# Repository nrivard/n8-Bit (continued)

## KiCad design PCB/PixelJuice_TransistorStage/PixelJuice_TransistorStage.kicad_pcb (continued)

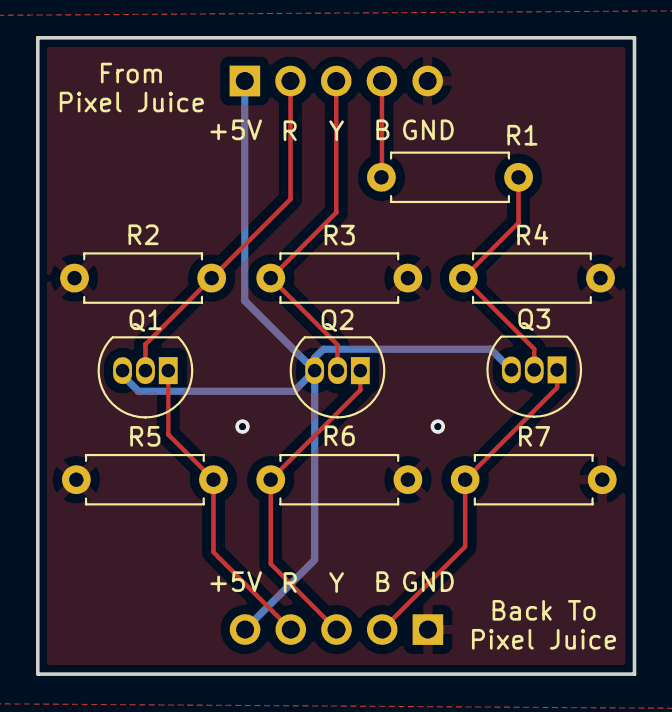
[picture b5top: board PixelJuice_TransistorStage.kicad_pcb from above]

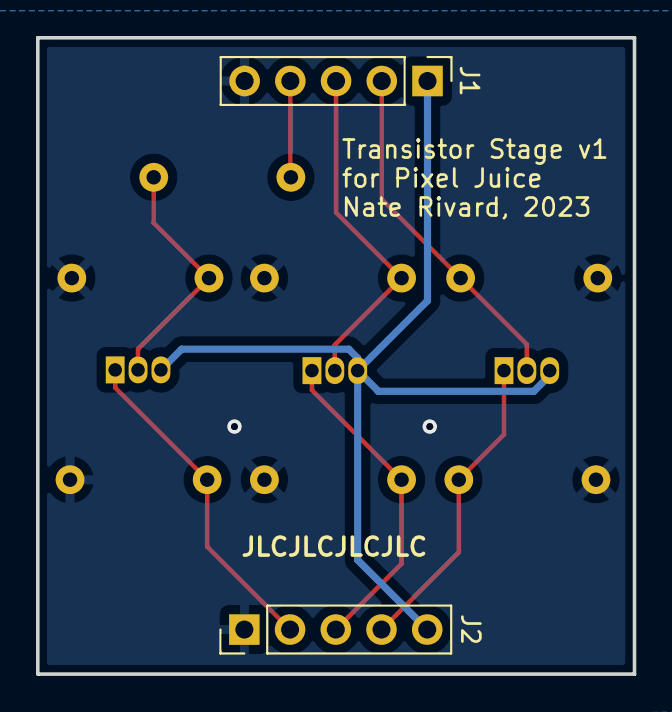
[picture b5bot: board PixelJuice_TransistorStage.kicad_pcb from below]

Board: 2 copper layers, 33.2 x 35.3 mm, 12 parts (2 on the bottom side), 9 nets.

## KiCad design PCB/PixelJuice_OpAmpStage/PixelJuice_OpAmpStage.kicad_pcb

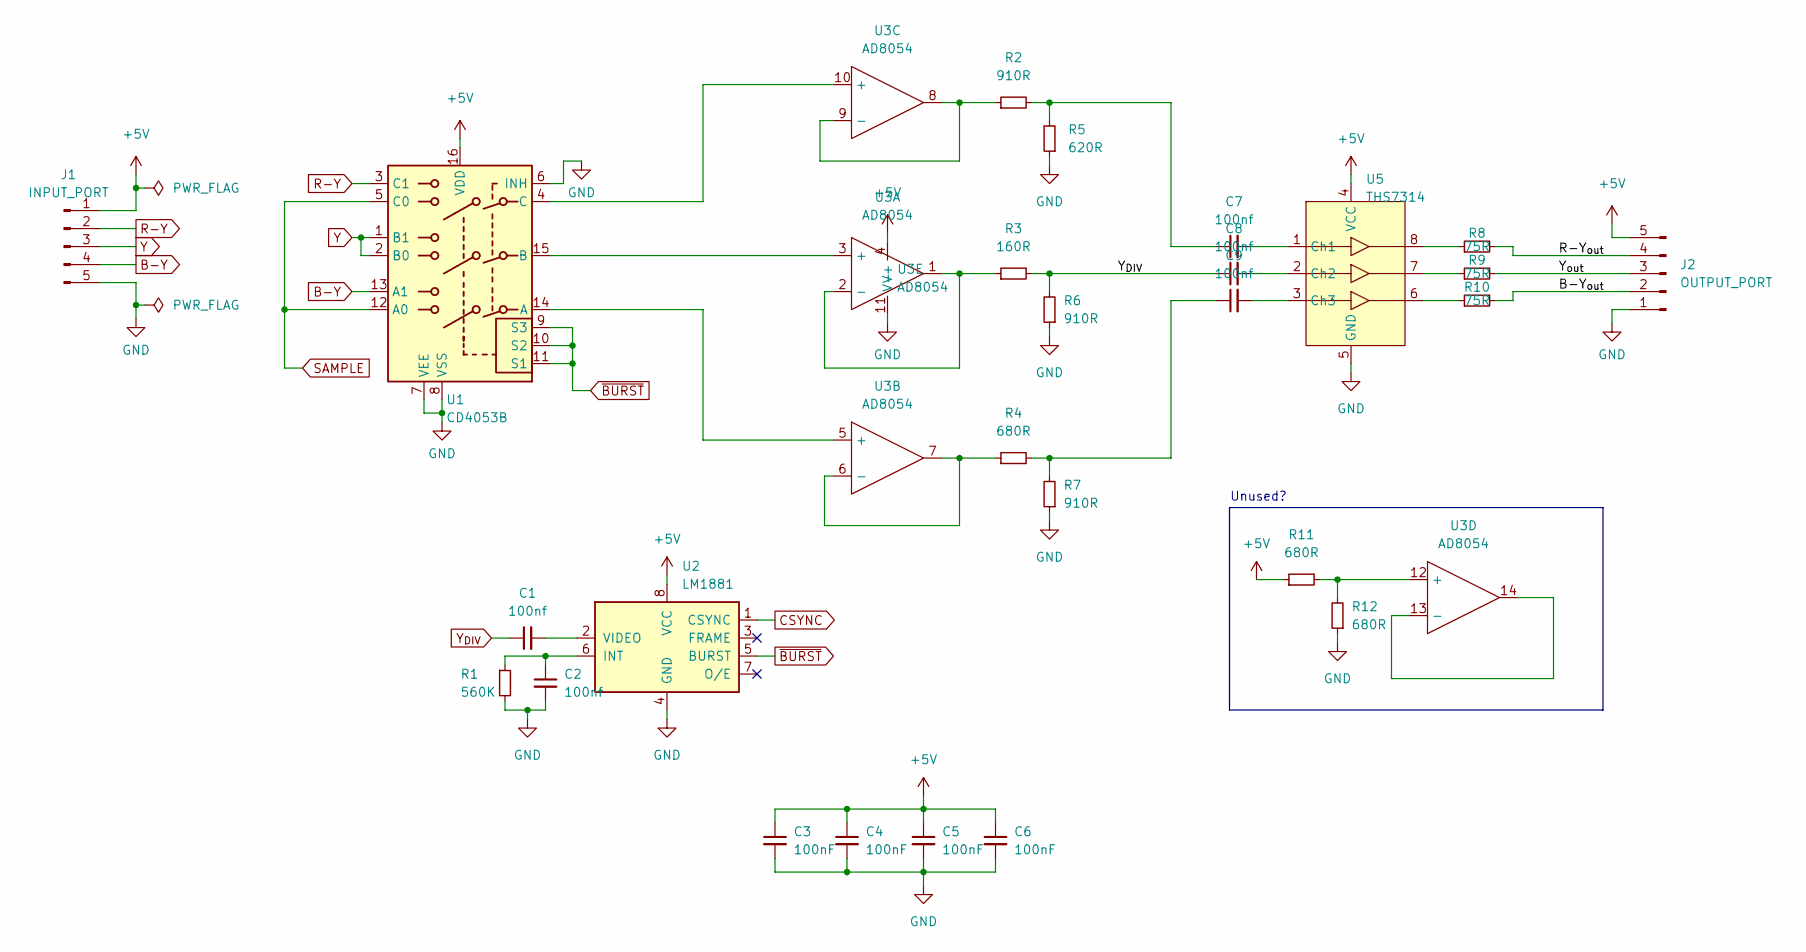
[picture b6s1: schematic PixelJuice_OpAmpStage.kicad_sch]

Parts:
C1, C2, C7, C8, C9: 100nf; C_0805_2012Metric_Pad1.18x1.45mm_HandSolder
C3, C4, C5, C6: 100nF; C_0805_2012Metric_Pad1.18x1.45mm_HandSolder
J1: INPUT_PORT; PinHeader_1x05_P2.54mm_Vertical
J2: OUTPUT_PORT; PinHeader_1x05_P2.54mm_Vertical
R1: 560K; R_0805_2012Metric_Pad1.20x1.40mm_HandSolder
R2, R6, R7: 910R; R_0805_2012Metric_Pad1.20x1.40mm_HandSolder
R3: 160R; R_0805_2012Metric_Pad1.20x1.40mm_HandSolder
R4, R11, R12: 680R; R_0805_2012Metric_Pad1.20x1.40mm_HandSolder
R5: 620R; R_0805_2012Metric_Pad1.20x1.40mm_HandSolder
R8, R9, R10: 75R; R_0805_2012Metric_Pad1.20x1.40mm_HandSolder
U1: CD4053B; DIP-16_W7.62mm_Socket
U2: LM1881; DIP-8_W7.62mm
U3: AD8054; SOIC-14_3.9x8.7mm_P1.27mm
U5: THS7314; SOIC-8_3.9x4.9mm_P1.27mm

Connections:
+5V: C3.1, C4.1, C5.1, C6.1, J1.1, J2.5, R11.1, U1.16 (VDD), U2.8 (VCC), U3.4 (V+), U5.4 (VCC)
/B-Y_{out}: J2.2, R10.2
/R-Y_{out}: J2.4, R8.2
/Y_{out}: J2.3, R9.2
B-Y: J1.4, U1.13 (A1)
CSYNC: U2.1 (CSYNC)
GND: C2.2, C3.2, C4.2, C5.2, C6.2, J1.5, J2.1, R1.2, R5.1, R6.1, R7.1, R12.1, U1.6 (INH), U1.7 (VEE), U1.8 (VSS), U2.4 (GND), U3.11 (V-), U5.5 (GND)
unnamed: C1.2, U2.2 (VIDEO)
unnamed: C2.1, R1.1, U2.6 (INT)
unnamed: C7.1, R2.2, R5.2
unnamed: C7.2, U5.1 (Ch1)
unnamed: C8.2, U5.2 (Ch2)
unnamed: C9.1, R4.2, R7.2
unnamed: C9.2, U5.3 (Ch3)
unnamed: R2.1, U3.8, U3.9 (-)
unnamed: R3.1, U3.1, U3.2 (-)
unnamed: R4.1, U3.6 (-), U3.7
unnamed: R8.1, U5.8
unnamed: R9.1, U5.7
unnamed: R10.1, U5.6
unnamed: R11.2, R12.2, U3.12 (+)
unnamed: U1.4 (C), U3.10 (+)
unnamed: U1.14 (A), U3.5 (+)
unnamed: U1.15 (B), U3.3 (+)
unnamed: U3.13 (-), U3.14
R-Y: J1.2, U1.3 (C1)
SAMPLE: U1.5 (C0), U1.12 (A0)
Y: J1.3, U1.1 (B1), U1.2 (B0)
Y_{DIV}: C1.1, C8.1, R3.2, R6.2
~BURST: U1.9 (S3), U1.10 (S2), U1.11 (S1), U2.5 (BURST)

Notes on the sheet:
Unused?

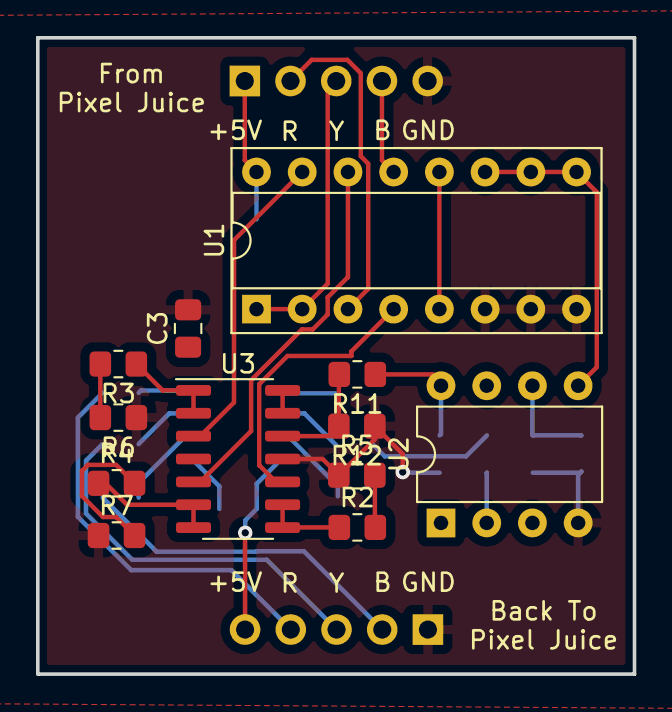
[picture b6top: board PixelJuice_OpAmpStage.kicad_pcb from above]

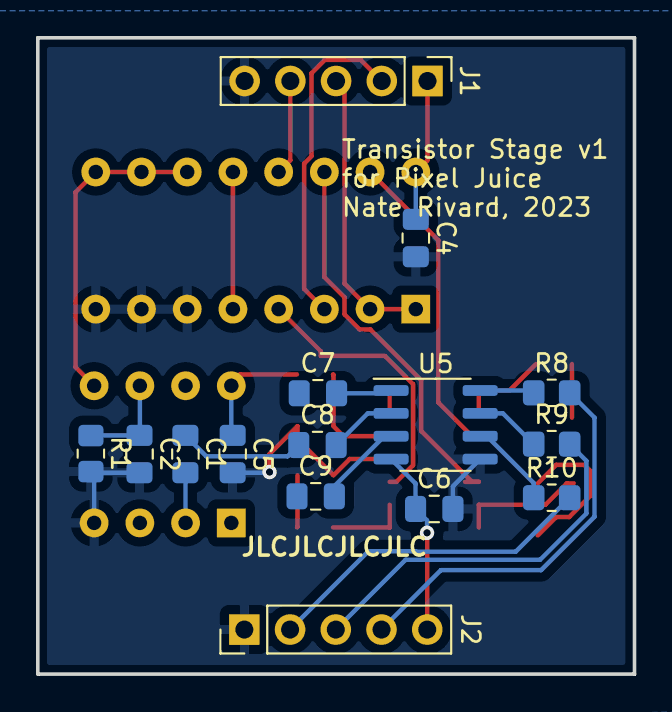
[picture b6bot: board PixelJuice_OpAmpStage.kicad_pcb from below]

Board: 2 copper layers, 33.2 x 35.4 mm, 27 parts (15 on the bottom side), 29 nets.

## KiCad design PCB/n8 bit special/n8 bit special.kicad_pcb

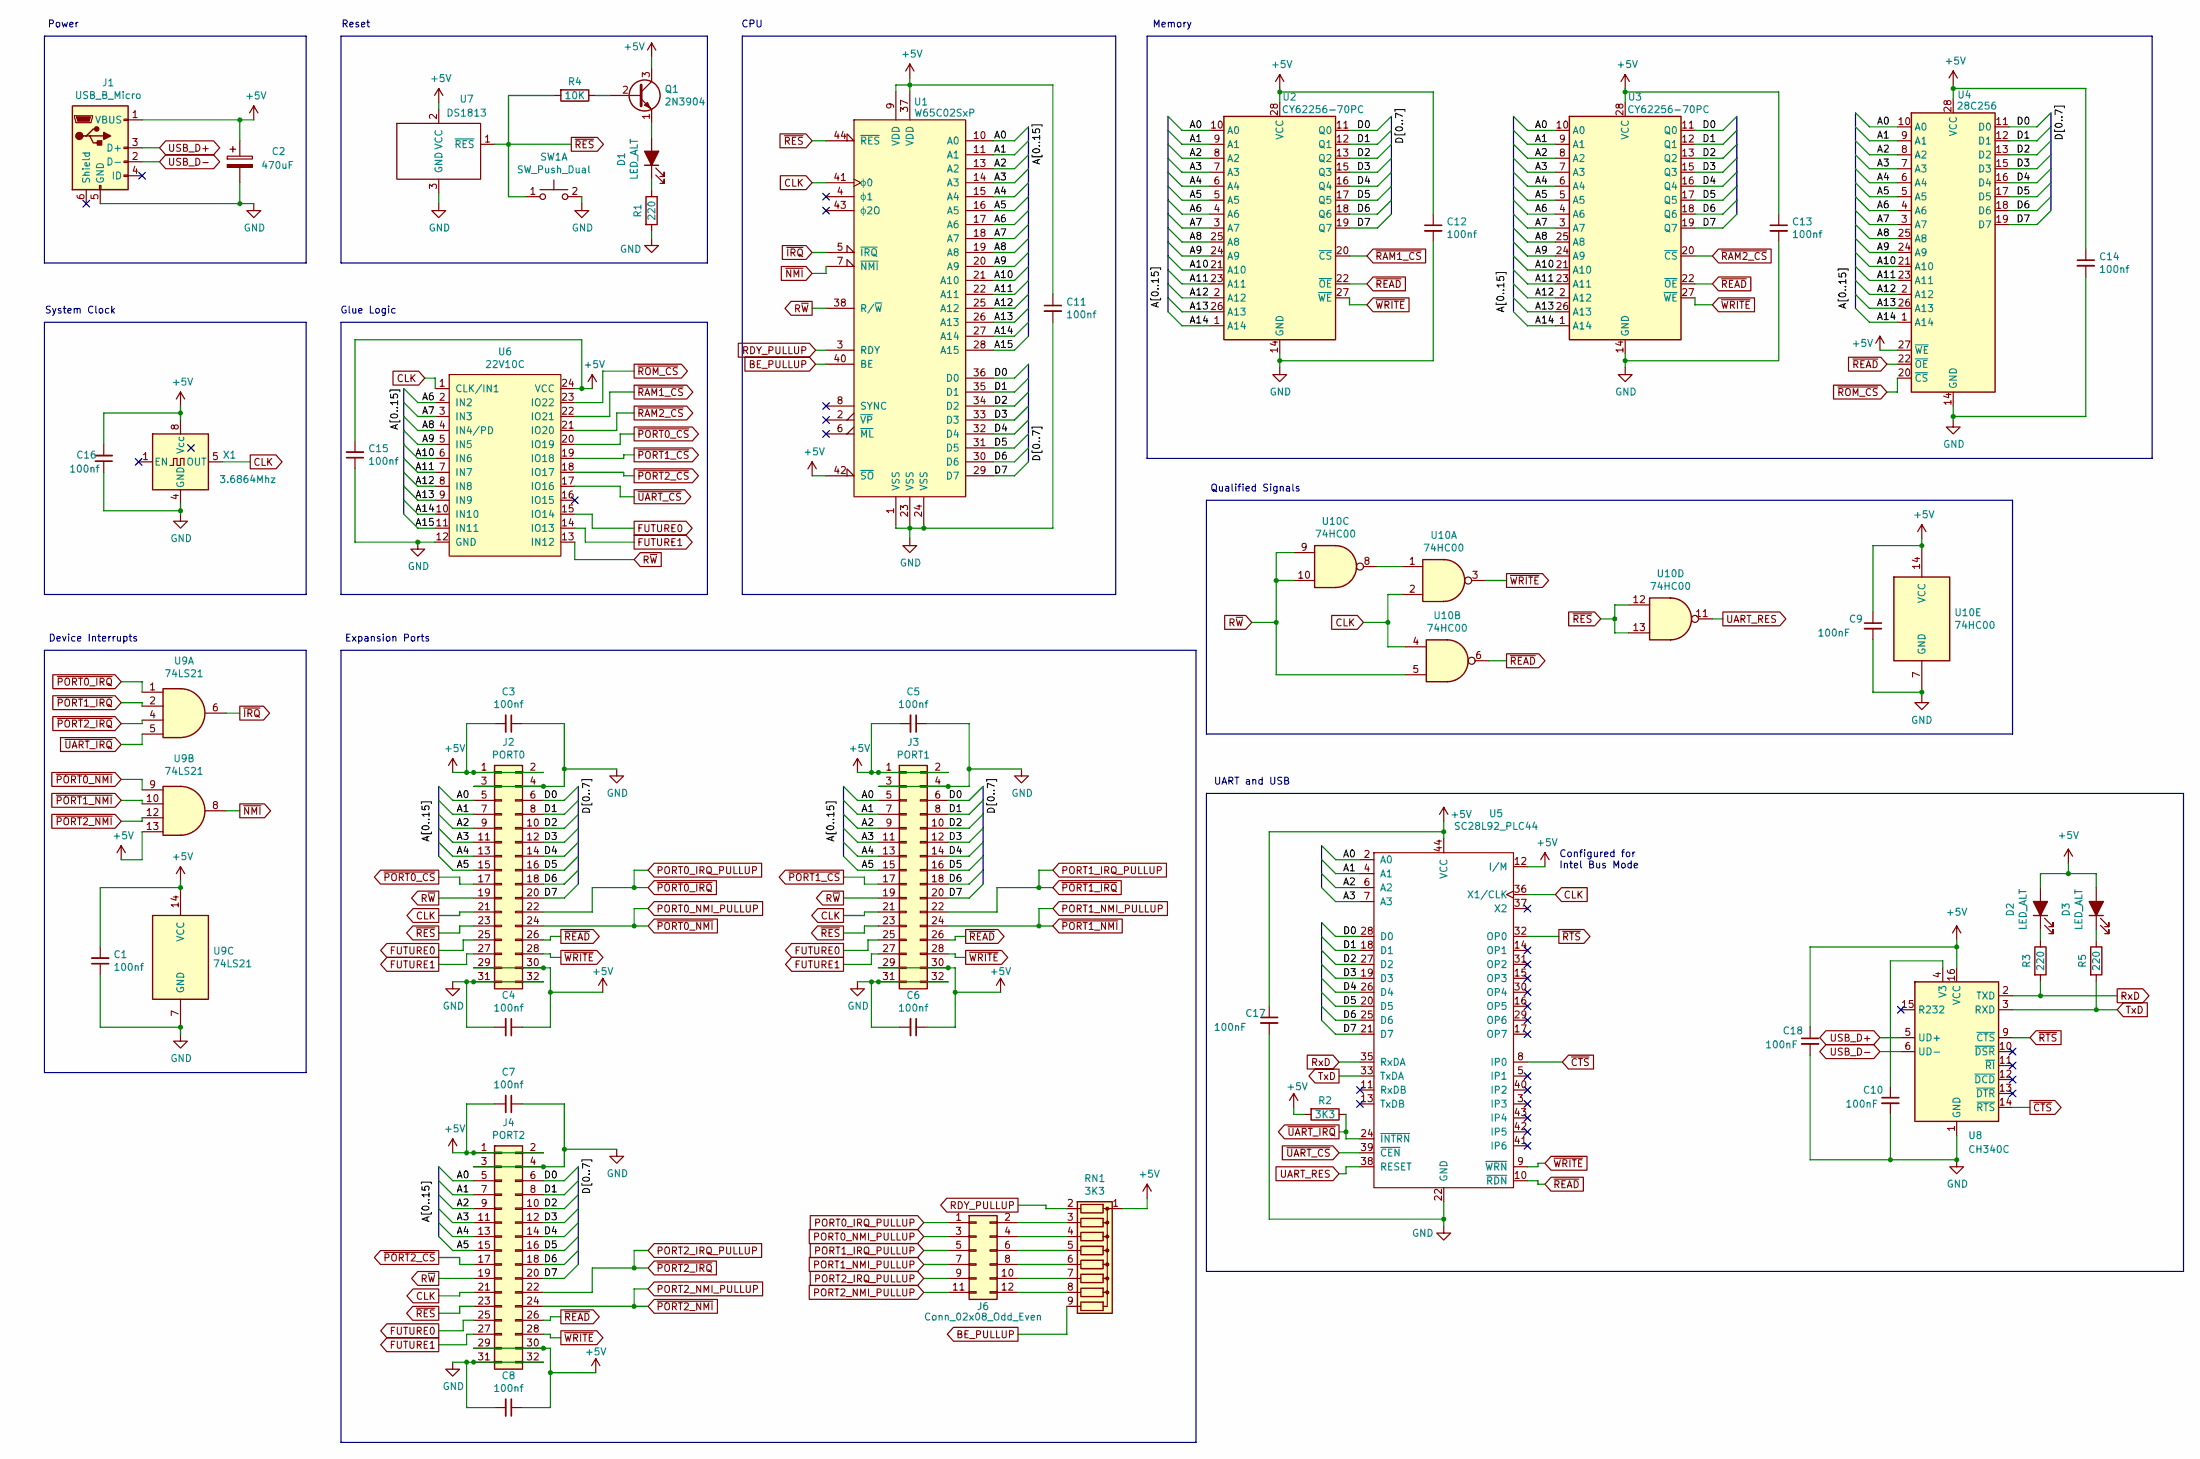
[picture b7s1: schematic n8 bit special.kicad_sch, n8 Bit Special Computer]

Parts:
C1, C3, C4, C5, C6, C7, C8, C11, C12, C13, C14, C15, C16: 100nf; C_Disc_D5.0mm_W2.5mm_P2.50mm
C2: 470uF; CP_Radial_D8.0mm_P3.80mm
C9, C10, C17, C18: 100nF; C_Disc_D5.0mm_W2.5mm_P2.50mm
D1, D2, D3: LED_ALT; LED_D3.0mm
J1: USB_B_Micro; USB_Micro-B_Wuerth_629105150521
J2: PORT0; PinSocket_2x16_P2.54mm_Vertical
J3: PORT1; PinSocket_2x16_P2.54mm_Vertical
J4: PORT2; PinSocket_2x16_P2.54mm_Vertical
J6: Conn_02x08_Odd_Even; PinHeader_2x06_P2.54mm_Vertical
Q1: 2N3904; TO-92
R1, R3, R5: 220; R_Axial_DIN0207_L6.3mm_D2.5mm_P7.62mm_Horizontal
R2: 3K3; R_Axial_DIN0207_L6.3mm_D2.5mm_P7.62mm_Horizontal
R4: 10K; R_Axial_DIN0207_L6.3mm_D2.5mm_P7.62mm_Horizontal
RN1: 3K3; R_Array_SIP9
SW1: SW_Push_Dual; SW_PUSH_6mm
U1: W65C02SxP; PLCC-44_THT-Socket
U2, U3: CY62256-70PC; DIP-28_W15.24mm_Socket
U4: 28C256; DIP-28_W15.24mm_Socket
U5: SC28L92_PLC44; PLCC-44_THT-Socket
U6: 22V10C; DIP-24_W7.62mm_Socket
U7: DS1813; TO-92; MANUFACTURER_PART_NUMBER ds181315+
U8: CH340C; SOIC-16_3.9x9.9mm_P1.27mm
U9: 74LS21; DIP-14_W7.62mm_Socket
U10: 74HC00; DIP-14_W7.62mm_Socket
X1: 3.6864Mhz; Oscillator_DIP-8

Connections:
+5V: C1.2, C2.1, C3.2, C4.1, C5.2, C6.1, C7.2, C8.1, C9.1, C11.1, C12.1, C13.1, C14.1, C15.2, C16.2, C17.1, C18.1, D2.2 (A), D3.2 (A), J1.1 (VBUS), J2.1, J2.2, J2.29, J2.30, J3.1, J3.2, J3.29, J3.30, J4.1, J4.2, J4.29, J4.30, Q1.3 (C), R2.2, RN1.1 (common), U1.9 (VDD), U1.37 (VDD), U1.42 (~SO), U2.28 (VCC), U3.28 (VCC), U4.27 (~WE), U4.28 (VCC), U5.12 (I/M), U5.44 (VCC), U6.24 (VCC), U7.2 (VCC), U8.16 (VCC), U9.13, U9.14 (VCC), U10.14 (VCC), X1.8 (Vcc)
/A0: J2.5, J3.5, J4.5, U1.10 (A0), U2.10 (A0), U3.10 (A0), U4.10 (A0), U5.2 (A0)
/A1: J2.7, J3.7, J4.7, U1.11 (A1), U2.9 (A1), U3.9 (A1), U4.9 (A1), U5.4 (A1)
/A2: J2.9, J3.9, J4.9, U1.13 (A2), U2.8 (A2), U3.8 (A2), U4.8 (A2), U5.6 (A2)
/A3: J2.11, J3.11, J4.11, U1.14 (A3), U2.7 (A3), U3.7 (A3), U4.7 (A3), U5.7 (A3)
/A4: J2.13, J3.13, J4.13, U1.15 (A4), U2.6 (A4), U3.6 (A4), U4.6 (A4)
/A5: J2.15, J3.15, J4.15, U1.16 (A5), U2.5 (A5), U3.5 (A5), U4.5 (A5)
/A6: U1.17 (A6), U2.4 (A6), U3.4 (A6), U4.4 (A6), U6.2 (IN2)
/A7: U1.18 (A7), U2.3 (A7), U3.3 (A7), U4.3 (A7), U6.3 (IN3)
/A8: U1.19 (A8), U2.25 (A8), U3.25 (A8), U4.25 (A8), U6.4 (IN4/PD)
/A9: U1.20 (A9), U2.24 (A9), U3.24 (A9), U4.24 (A9), U6.5 (IN5)
/A10: U1.21 (A10), U2.21 (A10), U3.21 (A10), U4.21 (A10), U6.6 (IN6)
/A11: U1.22 (A11), U2.23 (A11), U3.23 (A11), U4.23 (A11), U6.7 (IN7)
/A12: U1.25 (A12), U2.2 (A12), U3.2 (A12), U4.2 (A12), U6.8 (IN8)
/A13: U1.26 (A13), U2.26 (A13), U3.26 (A13), U4.26 (A13), U6.9 (IN9)
/A14: U1.27 (A14), U2.1 (A14), U3.1 (A14), U4.1 (A14), U6.10 (IN10)
/A15: U1.28 (A15), U6.11 (IN11)
/D0: J2.6, J3.6, J4.6, U1.36 (D0), U2.11 (Q0), U3.11 (Q0), U4.11 (D0), U5.28 (D0)
/D1: J2.8, J3.8, J4.8, U1.35 (D1), U2.12 (Q1), U3.12 (Q1), U4.12 (D1), U5.18 (D1)
/D2: J2.10, J3.10, J4.10, U1.34 (D2), U2.13 (Q2), U3.13 (Q2), U4.13 (D2), U5.27 (D2)
/D3: J2.12, J3.12, J4.12, U1.33 (D3), U2.15 (Q3), U3.15 (Q3), U4.15 (D3), U5.19 (D3)
/D4: J2.14, J3.14, J4.14, U1.32 (D4), U2.16 (Q4), U3.16 (Q4), U4.16 (D4), U5.26 (D4)
/D5: J2.16, J3.16, J4.16, U1.31 (D5), U2.17 (Q5), U3.17 (Q5), U4.17 (D5), U5.20 (D5)
/D6: J2.18, J3.18, J4.18, U1.30 (D6), U2.18 (Q6), U3.18 (Q6), U4.18 (D6), U5.25 (D6)
/D7: J2.20, J3.20, J4.20, U1.29 (D7), U2.19 (Q7), U3.19 (Q7), U4.19 (D7), U5.21 (D7)
BE_PULLUP: RN1.9 (R8), U1.40 (BE)
CLK: J2.21, J3.21, J4.21, U1.41 (ϕ0), U5.36 (X1/CLK), U6.1 (CLK/IN1), U10.2, U10.4, X1.5 (OUT)
FUTURE0: J2.25, J3.25, J4.25, U6.15 (IO14)
FUTURE1: J2.27, J3.27, J4.27, U6.14 (IO13)
GND: C1.1, C2.2, C3.1, C4.2, C5.1, C6.2, C7.1, C8.2, C9.2, C10.2, C11.2, C12.2, C13.2, C14.2, C15.1, C16.1, C17.2, C18.2, J1.5 (GND), J2.3, J2.4, J2.31, J2.32, J3.3, J3.4, J3.31, J3.32, J4.3, J4.4, J4.31, J4.32, R1.2, SW1.2 (D), U1.1 (VSS), U1.23 (VSS), U1.24 (VSS), U2.14 (GND), U3.14 (GND), U4.14 (GND), U5.22 (GND), U6.12 (GND), U7.3 (GND), U8.1 (GND), U9.7 (GND), U10.7 (GND), X1.4 (GND)
unnamed: C10.1, U8.4 (V3)
unnamed: D1.1 (K), R1.1
unnamed: D1.2 (A), Q1.1 (E)
unnamed: D2.1 (K), R3.1
unnamed: D3.1 (K), R5.1
unnamed: J6.2, RN1.3 (R2)
unnamed: J6.4, RN1.4 (R3)
unnamed: J6.6, RN1.5 (R4)
unnamed: J6.8, RN1.6 (R5)
unnamed: J6.10, RN1.7 (R6)
unnamed: J6.12, RN1.8 (R7)
unnamed: Q1.2 (B), R4.1
unnamed: U10.1, U10.8
PORT0_IRQ_PULLUP: J2.22, J6.1, U9.1
PORT0_NMI_PULLUP: J2.24, J6.3, U9.9
PORT1_IRQ_PULLUP: J3.22, J6.5, U9.2
PORT1_NMI_PULLUP: J3.24, J6.7, U9.10
PORT2_IRQ_PULLUP: J4.22, J6.9, U9.4
PORT2_NMI_PULLUP: J4.24, J6.11, U9.12
RDY_PULLUP: RN1.2 (R1), U1.3 (RDY)
RxD: R3.2, U5.35 (RxDA), U8.2 (TXD)
R~W: J2.19, J3.19, J4.19, U1.38 (R/~W), U6.13 (IN12), U10.5, U10.9, U10.10
TxD: R5.2, U5.33 (TxDA), U8.3 (RXD)
UART_RES: U5.38 (RESET), U10.11
USB_D+: J1.3 (D+), U8.5 (UD+)
USB_D-: J1.2 (D-), U8.6 (UD-)
~CTS: U5.8 (IP0), U8.14 (~RTS)
~IRQ: U1.5 (~IRQ), U9.6
~NMI: U1.7 (~NMI), U9.8
~PORT0_CS: J2.17, U6.20 (IO19)
~PORT1_CS: J3.17, U6.19 (IO18)
~PORT2_CS: J4.17, U6.18 (IO17)
~RAM1_CS: U2.20 (~CS), U6.22 (IO21)
~RAM2_CS: U3.20 (~CS), U6.21 (IO20)
~READ: J2.26, J3.26, J4.26, U2.22 (~OE), U3.22 (~OE), U4.22 (~OE), U5.10 (~RDN), U10.6
~RES: J2.23, J3.23, J4.23, R4.2, SW1.1 (C), U1.44 (~RES), U7.1 (~RES), U10.12, U10.13
~ROM_CS: U4.20 (~CS), U6.23 (IO22)
~RTS: U5.32 (OP0), U8.9 (~CTS)
~UART_CS: U5.39 (~CEN), U6.17 (IO16)
~UART_IRQ: R2.1, U5.24 (~INTRN), U9.5
~WRITE: J2.28, J3.28, J4.28, U2.27 (~WE), U3.27 (~WE), U5.9 (~WRN), U10.3

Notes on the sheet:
Expansion Ports
UART and USB
Memory
Configured for Intel Bus Mode
CPU
Power
Reset
Qualified Signals
Glue Logic
System Clock
Device Interrupts

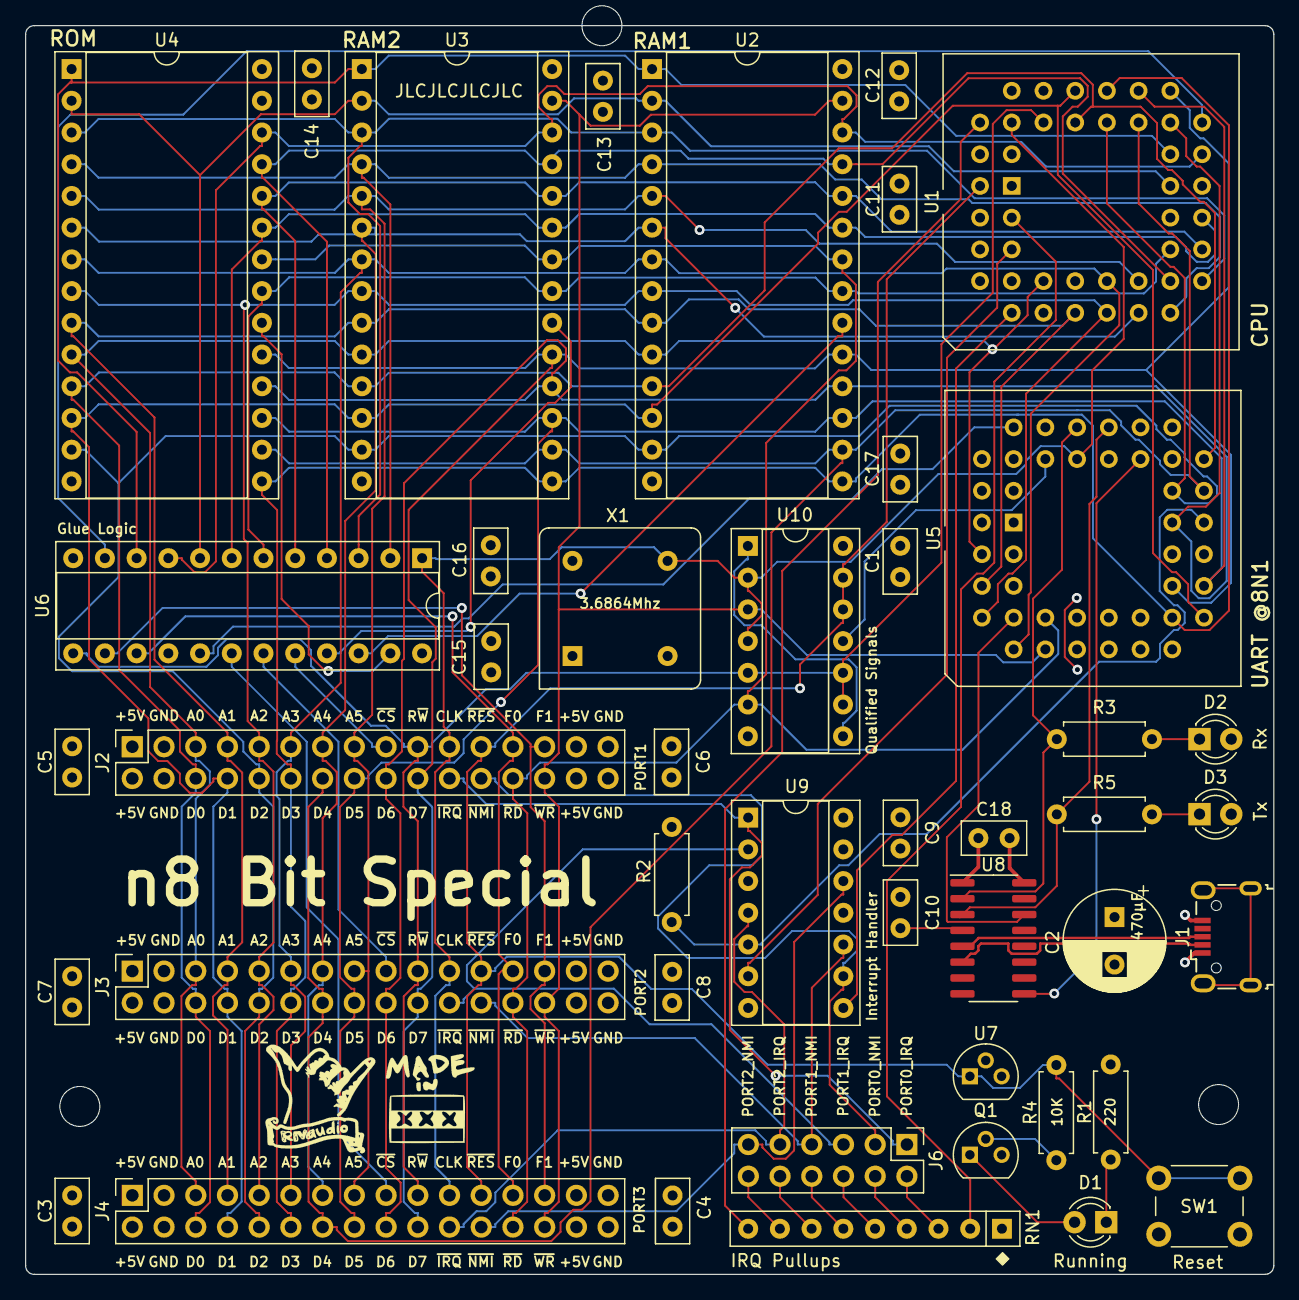
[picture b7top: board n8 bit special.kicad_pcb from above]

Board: 4 copper layers, 99.9 x 100.0 mm, 47 parts (0 on the bottom side), 71 nets.

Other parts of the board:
G1: LOGO; Shaka
G2: LOGO; MadeInAMS

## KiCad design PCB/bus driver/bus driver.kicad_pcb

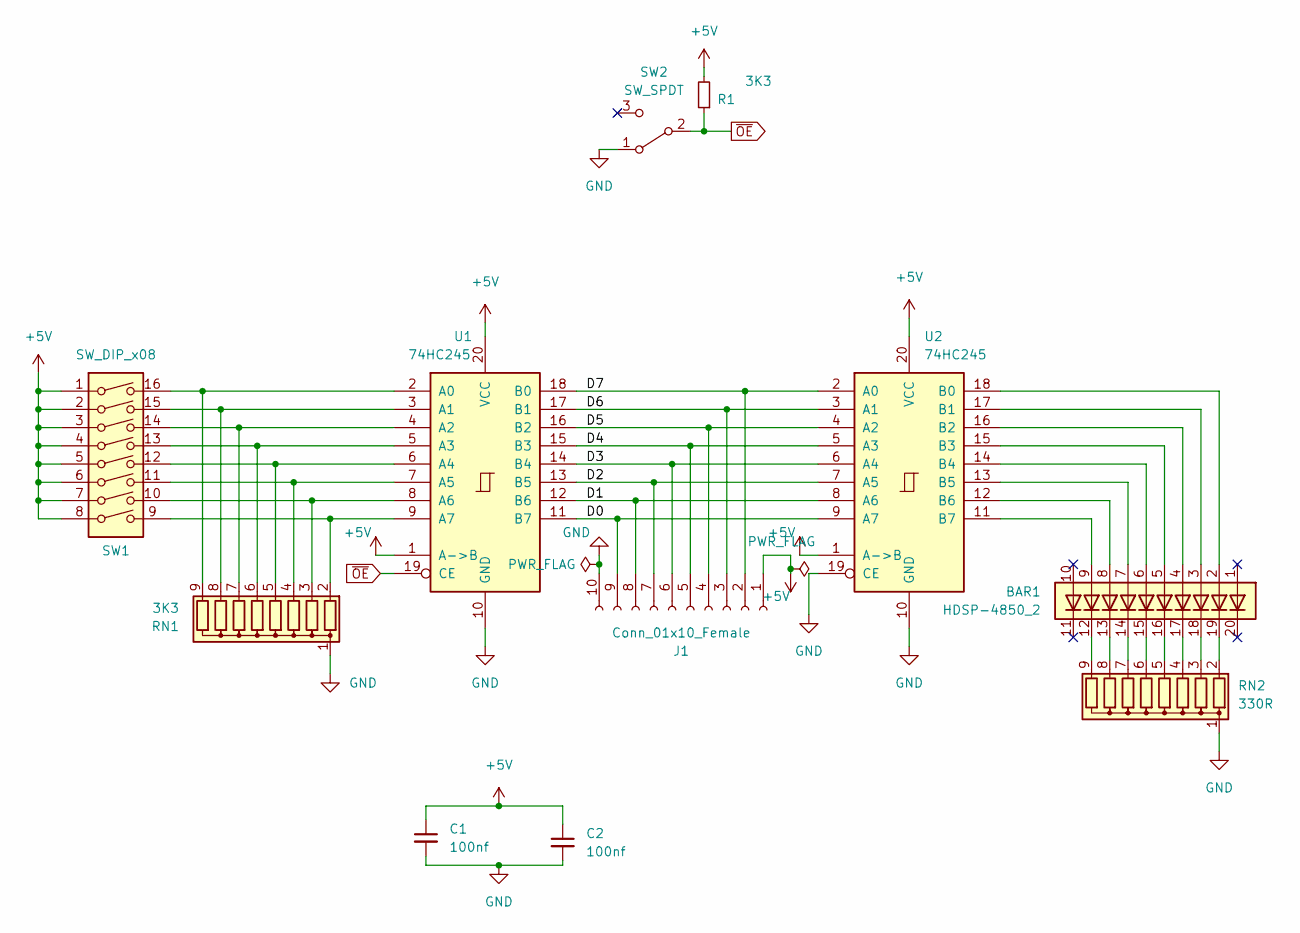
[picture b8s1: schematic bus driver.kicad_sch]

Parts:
BAR1: HDSP-4850_2; HDSP-4850
C1, C2: 100nf; C_Disc_D5.0mm_W2.5mm_P2.50mm
J1: Conn_01x10_Female; PinSocket_1x10_P2.54mm_Vertical
R1: 3K3; R_Axial_DIN0207_L6.3mm_D2.5mm_P7.62mm_Horizontal
RN1: 3K3; R_Array_SIP9
RN2: 330R; R_Array_SIP9
SW1: SW_DIP_x08; SW_DIP_SPSTx08_Slide_9.78x22.5mm_W7.62mm_P2.54mm
SW2: SW_SPDT; PinHeader_1x03_P2.54mm_Vertical
U1, U2: 74HC245; DIP-20_W7.62mm

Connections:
+5V: C1.1, C2.1, J1.1, R1.2, SW1.1, SW1.2, SW1.3, SW1.4, SW1.5, SW1.6, SW1.7, SW1.8, U1.1 (A->B), U1.20 (VCC), U2.1 (A->B), U2.20 (VCC)
/D0: J1.9, U1.11 (B7), U2.9 (A7)
/D1: J1.8, U1.12 (B6), U2.8 (A6)
/D2: J1.7, U1.13 (B5), U2.7 (A5)
/D3: J1.6, U1.14 (B4), U2.6 (A4)
/D4: J1.5, U1.15 (B3), U2.5 (A3)
/D5: J1.4, U1.16 (B2), U2.4 (A2)
/D6: J1.3, U1.17 (B1), U2.3 (A1)
/D7: J1.2, U1.18 (B0), U2.2 (A0)
GND: C1.2, C2.2, J1.10, RN1.1 (common), RN2.1 (common), SW2.1 (A), U1.10 (GND), U2.10 (GND), U2.19 (CE)
unnamed: BAR1.2 (A), U2.18 (B0)
unnamed: BAR1.3 (A), U2.17 (B1)
unnamed: BAR1.4 (A), U2.16 (B2)
unnamed: BAR1.5 (A), U2.15 (B3)
unnamed: BAR1.6 (A), U2.14 (B4)
unnamed: BAR1.7 (A), U2.13 (B5)
unnamed: BAR1.8 (A), U2.12 (B6)
unnamed: BAR1.9 (A), U2.11 (B7)
unnamed: BAR1.12 (K), RN2.9 (R8)
unnamed: BAR1.13 (K), RN2.8 (R7)
unnamed: BAR1.14 (K), RN2.7 (R6)
unnamed: BAR1.15 (K), RN2.6 (R5)
unnamed: BAR1.16 (K), RN2.5 (R4)
unnamed: BAR1.17 (K), RN2.4 (R3)
unnamed: BAR1.18 (K), RN2.3 (R2)
unnamed: BAR1.19 (K), RN2.2 (R1)
unnamed: RN1.2 (R1), SW1.9, U1.9 (A7)
unnamed: RN1.3 (R2), SW1.10, U1.8 (A6)
unnamed: RN1.4 (R3), SW1.11, U1.7 (A5)
unnamed: RN1.5 (R4), SW1.12, U1.6 (A4)
unnamed: RN1.6 (R5), SW1.13, U1.5 (A3)
unnamed: RN1.7 (R6), SW1.14, U1.4 (A2)
unnamed: RN1.8 (R7), SW1.15, U1.3 (A1)
unnamed: RN1.9 (R8), SW1.16, U1.2 (A0)
~OE: R1.1, SW2.2 (B), U1.19 (CE)

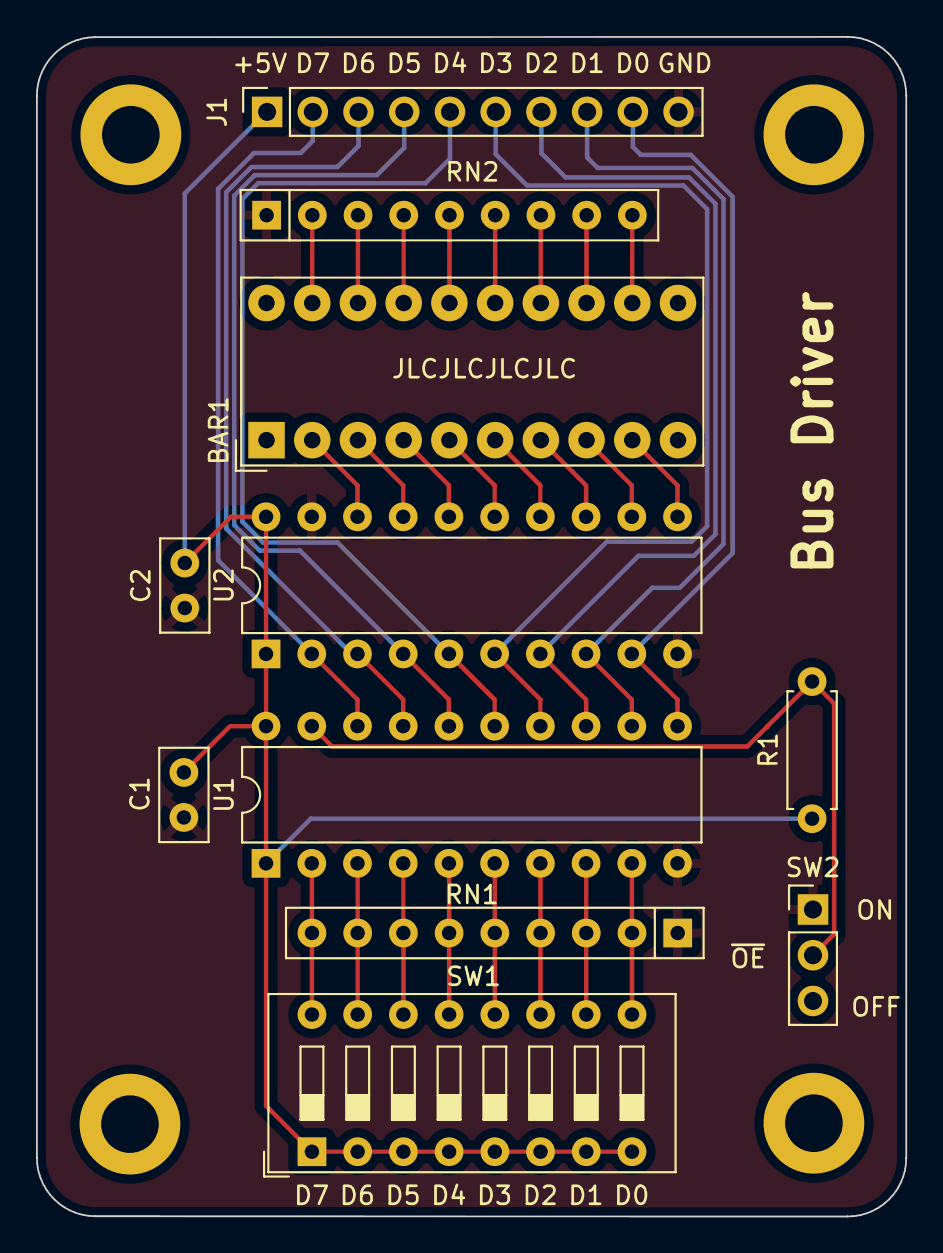
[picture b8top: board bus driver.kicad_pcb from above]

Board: 2 copper layers, 48.3 x 65.5 mm, 11 parts (0 on the bottom side), 35 nets.

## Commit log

2021-09-01 V1 of n8 Bit Special
    This is the V1 hardware schematic + PCBs that were actually printed. This includes a *hardware defect* where voltage was not stable bc the LED caused a voltage drop. This is fixed in V2 via an additi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
    Lastly, the GAL logic here _does_ include a fix. Previously, both RAM_CS signals were _not qualified_ with phi2. This is bad! So this version includes a GA
2021-09-01 Wrote proper README
2021-09-01 Updated README and bodge wire picture
2021-09-02 Removed unnecessary disk files
2021-09-02 More README clarifications
2021-09-06 New placement and parts for v2
2021-09-06 Used Freerouter to route 4 layer PCB
    Had to touch up inner well area on the UART as it was disconnected to the rest of the power plane.
2021-09-07 Layout centered around USB D+/D- differential pair
2021-09-07 v2 release candidate
2021-09-08 Cleanup
2021-11-30 Prep for n8 bus pinout changes
2021-11-30 n8 bus card template updated
2022-01-05 release candidate for v2
2022-01-05 asdf
2022-01-05 v2 of viaduct
2022-04-22 v2 changes
2022-05-15 Converted USB chip to CH340C which is more available Converted USB chip to CH340C which is more available and easier to solder :)
2022-05-16 Pre-import stage of autorouting
2022-05-20 Fixed D+/D- miswiring
2022-08-05 Final changes for v2
2023-02-21 expansion board revisions
2023-02-21 Updated README to match v2
2023-02-21 Fixed tiny typo in README
2023-02-26 Start of VDP based gfx card
2023-02-28 horizontal layout for vram but i want to try vertical
2023-03-23 Video card + bus driver changes
2023-03-29 going to make v1 of the video card modular
2023-03-29 Added amp stages
2023-04-14 rc1 before library swap test
2024-01-19 added 2 new soundcard designs
2024-10-16 Worked on Spi master a little bit
2024-10-21 Working simulation...
2024-10-22 Moved sub-circuits to top level for better visualization Fixed a bug with ITC being set on /RES Tracked down that inconsistent MOSI output is due to '165 being LEVEL sensitive not EDGE sensitive (no 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
2024-10-24 circuit in Digital is working, tested in real world
2024-10-25 3 signals away from SPI Master PCB
2024-11-04 rc1 for SPI Gate (prev SPI master) rc1 for Bouncer
2025-07-02 Added SpiMaster support
